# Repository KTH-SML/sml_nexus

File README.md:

# SML Nexus
Repositotry for code and documentation on the customized Nexus 4WD holonomic robots of the SML (Smart Mobility Lab) of KTH.

# Using the Nexus Robot
## Bringing up the Nexus robot
Every Nexus robot includes a companion computer (usually a NVidia TX2) connected to the internal Arduino low-level controller. To use the Nexus, one needs first to connect by SSH to the companion computer (credentials available by asking a lab member, replace COMPANION_COMPUTER_IP by the companion computer IP):

 `ssh sml@COMPANION_COMPUTER_IP`
 
Then the ROS_MASTER_URI and ROS_IP environnement variables need to be set accordingly. Check [ROS network setup ](http://wiki.ros.org/ROS/NetworkSetup) for more information.

To bring up the robot, run the following launch file from the companion computer:

 `roslaunch sml_nexus_robot sml_nexus_bringup.launch`
 
 After a successful launch, command and feedback topics should be available under the namespace **/nexus_ROBOT_ID**
 
## Sending commands
The robot can be commanded in velocity by publishing [ROS Twist message](http://docs.ros.org/melodic/api/geometry_msgs/html/msg/Twist.html) on the topic **/nexus_ROBOT_ID/cmd_vel**

## Receiving feedback
TODO
 
# Robot description
The robot is a modified 4 mecanum wheel holonomic robot from Nexus Robotics (https://www.nexusrobot.com/product/4wd-mecanum-wheel-mobile-arduino-robotics-car-10011.html).

## Characteristics
* **max speed:** 0.6m/s forward
* **wheel base:** 300mm

## Actuators
 * **Motors:** (4x) Faulhaber 12V DC Coreless Motor 16002, with 45° 50mm radius mecanum wheel. 
 * **Optional manipulator:** Either a **Robotis ViperX 250** or a **Robotis WidowX** depending on the platform.

## Controllers
 * **Onboard computer:** Either **NVidia TX2**, **NVidia Jetson Nano** or **Intel NUC** depending on the platform.
 * **Low-level controller:** Arduino Mega for interfacing with motor drivers, ultrasonic range sensor and encoders.
 * **Motor drivers:** Two Cytron MDD3A motor drivers.
 
## Sensors
* **(4x) Encoders:** Encoder on each wheel with a resolution of 12CPR before motor gearbox and 768CPR after gearbox.
* **(4x) Ultrasonic range sensor:** URM04 v1.0 ultrasonic range sensors with RS-485 interface.

# ROS package description
Packages:
* **sml_nexus_description**
* **sml_nexus_robot**

## sml_nexus_description
Contains the robot URDF description and meshes.

### Launch files
* **sml_nexus_description.launch:** Load the SML nexus 4WD mecanum robot description parameter and the robot state publisher.

* **sml_nexus_rviz.launch:** Load the SML nexus 4WD mecanum robot description parameter and a RViz session.

## sml_nexus_robot
Package to be run from the robot onboard computer.
### Launch files
* **sml_nexus_bringup.launch:** Load config files and connect to the low-level controller using rosserial.

### Config files
* **nexus_pid_params.yaml** Parameters of the motor controllers

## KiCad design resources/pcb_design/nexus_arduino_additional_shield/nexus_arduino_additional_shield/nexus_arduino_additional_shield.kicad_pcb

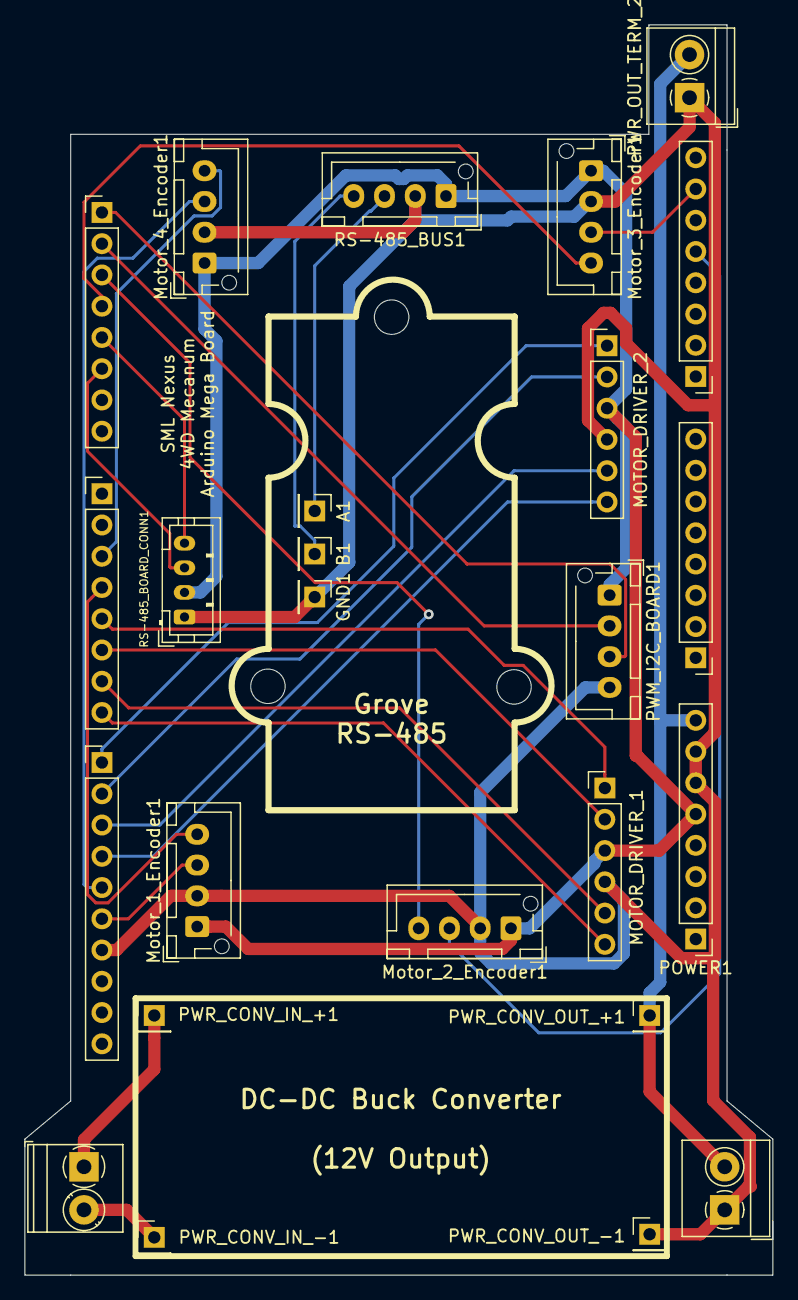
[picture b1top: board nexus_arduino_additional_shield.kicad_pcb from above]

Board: 2 copper layers, 60.8 x 101.6 mm, 25 parts (0 on the bottom side), 27 nets.

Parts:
A1: Conn_01x01_Male; PinHeader_1x01_P2.54mm_Vertical
ANALOG_PIN_1, ANALOG_PIN_2: Conn_01x08_Male; PinHeader_1x08_P2.54mm_Vertical
B1: Conn_01x01_Male; PinHeader_1x01_P2.54mm_Vertical
COMMUNICATION1: Conn_01x08_Male; PinHeader_1x08_P2.54mm_Vertical
GND1: Conn_01x01_Male; PinHeader_1x01_P2.54mm_Vertical
MOTOR_DRIVER_1, MOTOR_DRIVER_2: Conn_01x06_Male; PinHeader_1x06_P2.54mm_Vertical
Motor_1_Encoder1, Motor_2_Encoder1, Motor_3_Encoder1, Motor_4_Encoder1: Conn_01x04_Male; JST_XH_B4B-XH-AM_1x04_P2.50mm_Vertical
POWER1: Conn_01x08_Male; PinHeader_1x08_P2.54mm_Vertical
PWM_1: Conn_01x10_Male; PinHeader_1x10_P2.54mm_Vertical
PWM_2: Conn_01x08_Male; PinHeader_1x08_P2.54mm_Vertical
PWM_I2C_BOARD1: Conn_01x04_Male; JST_XH_B4B-XH-AM_1x04_P2.50mm_Vertical
PWR_CONV_IN_+1: Conn_01x01_Male; PinHeader_1x01_P2.54mm_Vertical
PWR_CONV_IN_-1: Conn_01x01_Male; PinHeader_1x01_P2.54mm_Vertical
PWR_CONV_OUT_+1: Conn_01x01_Male; PinHeader_1x01_P2.54mm_Vertical
PWR_CONV_OUT_-1: Conn_01x01_Male; PinHeader_1x01_P2.54mm_Vertical
PWR_IN_TERM1: Conn_01x02_Male; TerminalBlock_Phoenix_PT-1,5-2-3.5-H_1x02_P3.50mm_Horizontal
PWR_OUT_TERM_1, PWR_OUT_TERM_2: Conn_01x02_Male; TerminalBlock_4Ucon_1x02_P3.50mm_Horizontal
RS-485_BOARD_CONN1: Conn_01x04_Male; JST_PH_B4B-PH-K_1x04_P2.00mm_Vertical
RS-485_BUS1: Conn_01x04_Male; JST_XH_B4B-XH-AM_1x04_P2.50mm_Vertical

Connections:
/2: Motor_4_Encoder1.4, PWM_2.3
/3: Motor_1_Encoder1.4, PWM_2.4
/4: MOTOR_DRIVER_1.1, PWM_2.5
/5: MOTOR_DRIVER_1.2, PWM_2.6
/5V: MOTOR_DRIVER_1.3, MOTOR_DRIVER_2.3, Motor_1_Encoder1.1, Motor_2_Encoder1.1, Motor_3_Encoder1.1, Motor_4_Encoder1.1, POWER1.5, PWM_I2C_BOARD1.1, RS-485_BOARD_CONN1.2, RS-485_BUS1.1
/6: MOTOR_DRIVER_1.5, PWM_2.7
/7: MOTOR_DRIVER_1.6, PWM_2.8
/8: MOTOR_DRIVER_2.1, PWM_1.1
/9: MOTOR_DRIVER_2.2, PWM_1.2
/10: MOTOR_DRIVER_2.5, PWM_1.3
/11: MOTOR_DRIVER_2.6, PWM_1.4
/12: Motor_4_Encoder1.3, PWM_1.5
/13: Motor_1_Encoder1.3, PWM_1.6
/16: COMMUNICATION1.6, RS-485_BOARD_CONN1.3
/17: COMMUNICATION1.5, RS-485_BOARD_CONN1.4
/18: COMMUNICATION1.4, Motor_3_Encoder1.4
/19: COMMUNICATION1.3, Motor_2_Encoder1.4
/20: COMMUNICATION1.2, PWM_I2C_BOARD1.2
/21: COMMUNICATION1.1, PWM_I2C_BOARD1.3
/A12: ANALOG_PIN_2.5, Motor_2_Encoder1.3
/A14: ANALOG_PIN_2.7, Motor_3_Encoder1.3
/VIN: POWER1.8, PWR_CONV_OUT_+1.1, PWR_OUT_TERM_1.2, PWR_OUT_TERM_2.2
GND: GND1.1, MOTOR_DRIVER_1.4, MOTOR_DRIVER_2.4, Motor_1_Encoder1.2, Motor_2_Encoder1.2, Motor_3_Encoder1.2, Motor_4_Encoder1.2, POWER1.6, POWER1.7, PWM_1.7, PWM_I2C_BOARD1.4, PWR_CONV_OUT_-1.1, PWR_OUT_TERM_1.1, PWR_OUT_TERM_2.1, RS-485_BOARD_CONN1.1, RS-485_BUS1.2
unnamed: A1.1, RS-485_BUS1.3
unnamed: B1.1, RS-485_BUS1.4
unnamed: PWR_CONV_IN_+1.1, PWR_IN_TERM1.1
unnamed: PWR_CONV_IN_-1.1, PWR_IN_TERM1.2

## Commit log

2020-06-20 Added Arduino firmware
2020-06-20 Added launch file for robot bringup
2020-06-21 First readme commit
    Added bringup and sending command sections, as well as adding a skeleton for readme structure.
2020-06-22 Added motor data logging and analysis programs
    Motor speed relative to PWM command data is used to create a proper control for the robot.
    The data is logged and analysed through 2 MATLAB scripts. The proper firmware should be
    running in the low-level arduino controller so that the robot can answer to PWM commands.
2020-06-23 Replaced the feedforward gain with a polynomial
    A polynomial fits the velocity to PWM function better than a simple linear function.
    Polynomial gains are obtained by running the motors with different PWM value and
    logging the resulting velocities.
2020-06-23 Added default values for feedforward control
2020-06-23 Added feedforward polynomial coefficients to config file
2020-06-23 Added description to log and analysis Matlab scripts
2020-06-25 First functional version
2020-06-25 Updated gains in config
2020-06-26 Removed debug messages
2020-07-09 Add URDF robot description package
2020-07-10 Add limits to the velocity command
2020-07-14 Add range sensor plugin
2020-07-20 Fix missing group tag in launch file
2020-07-20 Fix broken group tag in launch file
2020-07-24 Add robot description and ROS package description
2020-07-27 Change to Cytron MDD3A motor driver and increased PWM frequency
2020-08-02 Change motor naming and control
    Reduce polynomial degree. Change motor naming to reverse direction (in order to
    have the robotic arm facing forward). Change PWM pins to accomodate for already
    used pins.
2020-08-02 Change motor control
    Change robot direction to be consitent with the firmware. Change PWM pins to fix
    an issue with pins needed for encoder interrupt.
2020-08-02 Stop ROS launch file if communication with low-level controller is lost
    The rosserial node is made required so that the whole launch file shutdowns if it
    crashed.
2020-08-02 Fix negative motor velocity command issue
    Calculating the polynomial directly with negative velocity creates issues as
    the polynomial function was created using only positive velocities. Fix the issue
    by using the absolute value of velocity for computing the polynomial PWM command
    and then getting the opposite value.
2020-08-02 Tune PID parameters after a tuning session.
    Tuning session of the day
2020-08-02 Fix angular velocity command
    Radius was calculated using mm with command was expressed in meters.
2020-08-03 Add min wheel speed parameter for each motor.
    Any PWM command sent to a motor is constrained by the motor minimum PWM value needed to start
    making it move. Maximum value is also constrained.
2020-08-03 Tune after tuning session
    Tuning session of the day.
2020-08-03 Fix error in wheel velocity command computation
2020-08-03 Add odometry broadcaster node, not yet functional
2020-08-10 Add odometry node, now building (untested)
2020-08-17 Add initialization of time and rotation quaternion (not tested)
    Add initialization of last received feedback time and initialization of odometry message unit
    quaternion.
2020-08-17 Fix bug when rotation without translation motion
    A division by zero was happening when the robot was rotating on the spot as the travelled
    distance was used to compute the arc radius. An if condition on the travelled distance
    solves this issue.
2020-08-18 Fix rotation bug and remove debug messages
2020-08-18 Fix negative Y axis bug and add timeout warning
2020-08-18 Updated controller params after tuning session
2020-08-18 Make rosserial node required in launch file
2020-08-18 Add odometry broadcaster node to bringup
2020-08-18 Resolve namespace missing slash. add log message and remove debug message
2020-08-18 Replace atan by atan2
2020-08-20 Use time interval from low-level controller
    The time interval used for computing odometry was the time difference between 2 messages from the low-level
    controller. This could add innacuracies in odometry if the communication was laggy. Time interval between
    two wheel velocity measurements is now directly given by the low-level controller along the 4 wheel
    velocities.
2020-08-20 Rotate sensor naming.
    Previous sensor naming was using the default Nexus Robotics heading of the robot. The SML adapted version
    is facing the other way so that any attached robotic arm would be facing forward. The sensor naming has
    been changed in this commit to reflect that.
2020-09-10 Change motor pins
2020-10-12 Add geometry message dependency
2020-10-12 Add missing run dependency
2020-12-01 Add move_base and navigation parameters (to test)
2020-12-02 Add move base implementation
2020-12-04 Fix issue in launch file regarding global planner
2021-02-16 Add params for nexus0
2021-02-16 Add nexus 0 bringup file
2021-02-17 Add timestamps to odom transform
2021-02-17 Remove namespace from standard bringup
2021-02-17 Change name from nexus_X to nexusX for compatibility reasons
2021-02-17 Add navigation capabilities to nexus robot
2021-02-18 Add nexus2 config and launch file
2021-02-22 Add local planner in dependencies
2021-02-23 Change base link and base footprint frames hierarchy
2021-02-23 Replace static tf publisher by robot state publisher
2021-02-23 Remove static tf publisher
2021-02-23 Fix URDF with replacing root link with dummy one
2021-02-23 Add frame id parameters
2021-02-24 Publish odom tf in gazebo simulation
2021-02-24 Add choice of local planner from argument
2021-02-24 Tuned goal tolerance of TEB local planner
2021-03-05 Tune local teb planner
2021-03-08 Add tf_prefix to launch file of nexus0
2021-03-08 Add tf_prefix to nexus2
2021-03-08 Fix typo
2021-03-09 Add nexus5 config
2021-06-03 Add arduino shield PCB design files
2021-08-06 Add nexus1 config and bringup file
2021-10-29 Fix encoder pin error
2021-10-29 Add doc pictures
2021-10-29 Add pictures
